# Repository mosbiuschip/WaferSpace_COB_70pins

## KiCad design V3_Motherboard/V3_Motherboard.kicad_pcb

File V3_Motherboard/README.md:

# MV3C_PCB_TEMP
Temporary View Repo for V3 Motherboard PCB (v4a_2026)

Changes from V1 Chip PCB (v3b_2025)

1. Pin bindings changed according to pin bindings .csv and WaferSpace_COB_70pins/V3_COB_Original, COB mounting footprint replaced chip socket
    a. Added Bus 1-5 pins, routed out through 2x3 header pin Breakout
    b. Removed NPAIR_4_BODY, PPAIR_4_BODY, ISINK_32 pins
    c. Changed trace width from standard .25 to .15

Further design considerations and questions

1. SOLVED: LDO - Already have voltage supply protection, is there any reason of convenience to keep LDO for 2.5V or other voltage
2. SOLVED: Power Net Switch - Is it desireable to have an aditional low drop mechanical switch for power net for chip safety
3. Feedback from V1 board - Are there any issues with original V1 design that need to be addressed

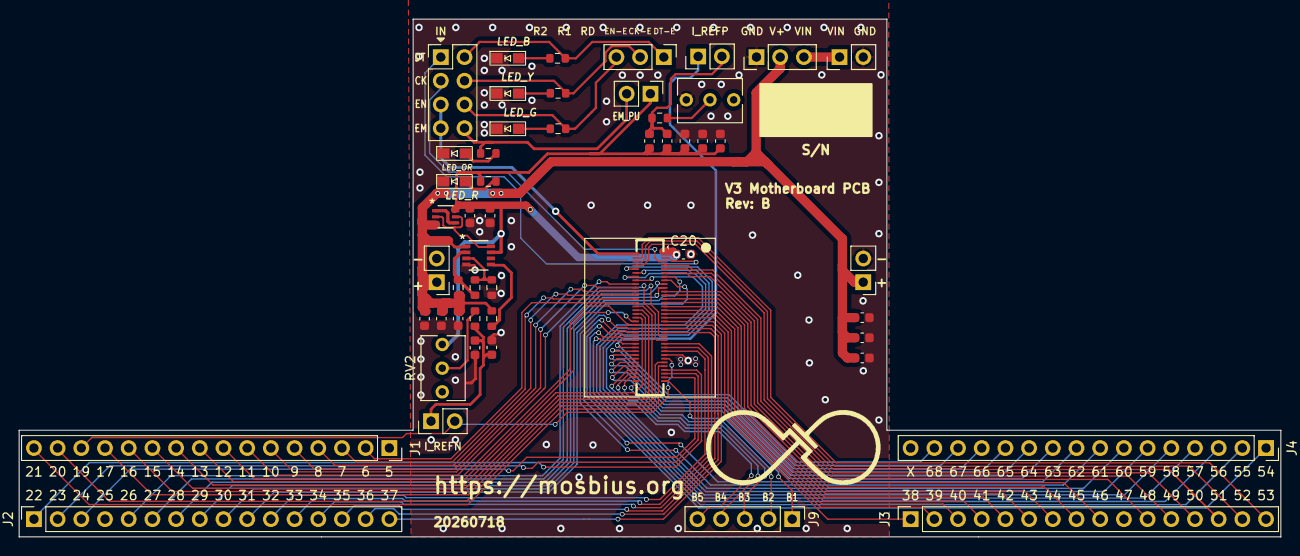
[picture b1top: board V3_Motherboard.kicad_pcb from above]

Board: 2 copper layers, 135.3 x 55.5 mm, 51 parts (0 on the bottom side), 90 nets.

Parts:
C1, C6, C8, C9, C15, C18: 1u; C_0603_1608Metric
C2, C3, C7, C10, C16, C17: 0.1u; C_0603_1608Metric
C12, C14, C19: 10u; C_0603_1608Metric
C20: 47u; C_0603_1608Metric
D1: LED_OR; SunLED_LED_XZC_0805
D2: LED_G; SunLED_LED_XZC_0805
D3: LED_Y; SunLED_LED_XZC_0805
D4: LED_B; SunLED_LED_XZC_0805
D5: LED_R; SunLED_LED_XZC_0805
J1, J2, J3, J4: Conn_01x16_Pin; PinSocket_1x16_P2.54mm_Vertical
J5, J7, J8: PINHD_1x2_Male; PinHeader_1x02_P2.54mm_Vertical
J6: Conn_01x02_Pin; PinHeader_1x02_P2.54mm_Vertical
J9: Conn_01x05_Pin; PinHeader_1x05_P2.54mm_Vertical
J10: Conn_02x04_Row_Letter_First; PinHeader_2x04_P2.54mm_Vertical
J14_GND2, J14_GND3: Conn_01x03; PinHeader_1x03_P2.54mm_Vertical
J18_VDC1: Conn_01x02; PinHeader_1x02_P2.54mm_Vertical
JP2_EN1: Jumper_2_Open; PinHeader_1x02_P2.54mm_Vertical
R7, R9, R17, R19: 330; R_0603_1608Metric
R8: 750; R_0603_1608Metric
R11, R18: 1.1k; R_0603_1608Metric
R13, R16: 0; R_0603_1608Metric
R14: 510K; R_0603_1608Metric
R15: 120K; R_0603_1608Metric
RV1, RV2: 25k_POT; Potentiometer_Bourns_3266Y_Vertical
U2: LTC4365TS8; TSOT-23_TS8_LIT
U3: UM6K34NTCN; TRANS_UM6J1_ROM
U4: P0.40_HC-PBB40C-70DS-0.4V-3.0-02_wscob

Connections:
/BUS1: J9.1, U4.35 (pad_46)
/BUS2: J9.2, U4.36 (pad_44)
/BUS3: J9.3, U4.37 (pad_43)
/BUS4: J9.4, U4.38 (pad_42)
/BUS5: J9.5, U4.39 (pad_41)
/CMFB_OTA2_INN: J4.2, U4.47 (pad_32)
/CMFB_OTA2_INP: J4.3, U4.46 (VDD_CORE)
/CMFB_OTA2_OUT: J4.1, U4.48 (pad_31)
/CM_N_IOUT_1: J1.15, U4.30 (pad_51)
/CM_N_IOUT_2: J1.16, U4.31 (pad_50)
/CM_N_IOUT_4: J2.1, U4.32 (pad_49)
/CM_N_IOUT_8: J2.2, U4.33 (pad_48)
/CM_N_IOUT_16: J2.3, U4.34 (pad_47)
/CM_N_IREF: J1.14, J7.2, U4.29 (pad_52)
/CM_N_IREF2: J2.5, U4.24 (VDD_IO)
/CM_N_IREF3: J2.6, U4.23 (pad_58)
/CM_P_IOUT_1: J4.14, U4.44 (VDD_IO)
/CM_P_IOUT_2: J4.13, U4.43 (pad_37)
/CM_P_IOUT_4: J4.12, U4.42 (pad_38)
/CM_P_IOUT_8: J4.11, U4.41 (pad_39)
/CM_P_IOUT_16: J4.10, U4.40 (pad_40)
/CM_P_IREF: J4.15, J8.1, U4.45 (GND)
/CM_P_IREF2: J4.9, U4.49 (pad_30)
/CM_P_IREF3: J4.8, U4.50 (pad_29)
/INV_TPLGY16_1INN: J3.14, U4.67 (pad_12)
/INV_TPLGY16_1INP: J3.16, U4.69 (pad_10)
/INV_TPLGY16_1OUT: J3.15, U4.68 (pad_11)
/INV_TPLGY16_2INN: J3.11, U4.6 (pad_2)
/INV_TPLGY16_2INP: J3.13, U4.4 (pad_4)
/INV_TPLGY16_2OUT: J3.12, U4.5 (pad_3)
/NMOS_4A_DRAIN: J2.8, U4.10 (GND)
/NMOS_4A_GATE: J2.7, U4.9 (VDD_IO)
/NMOS_4B_DRAIN: J2.10, U4.8 (pad_0)
/NMOS_4B_GATE: J2.9, U4.7 (pad_1)
/NPAIR_4A_DRAIN: J3.4, U4.16 (pad_65)
/NPAIR_4A_GATE: J3.5, U4.15 (pad_66)
/NPAIR_4A_SOURCE: J3.6, U4.14 (pad_67)
/NPAIR_4B_DRAIN: J3.9, U4.11 (VDD_CORE)
/NPAIR_4B_GATE: J3.8, U4.12 (pad_69)
/NPAIR_4B_SOURCE: J3.7, U4.13 (pad_68)
/NPAIR_A_DRAIN: J2.14, U4.22 (pad_59)
/NPAIR_A_GATE: J2.15, U4.21 (pad_60)
/NPAIR_A_SOURCE: J2.16, U4.20 (pad_61)
/NPAIR_B_DRAIN: J3.3, U4.17 (pad_64)
/NPAIR_B_GATE: J3.2, U4.18 (GND)
/NPAIR_B_SOURCE: J3.1, U4.19 (PWR_AUX)
/OTA_N_INN: J2.12, U4.26 (pad_55)
/OTA_N_INP: J2.11, U4.27 (pad_54)
/OTA_N_OUT: J2.13, U4.25 (GND)
/PMOS_4A_DRAIN: J4.4, U4.63 (pad_16)
/PMOS_4A_GATE: J4.5, U4.64 (pad_15)
/PMOS_4B_DRAIN: J4.6, U4.65 (pad_14)
/PMOS_4B_GATE: J4.7, U4.66 (pad_13)
/PPAIR_4A_DRAIN: J1.2, U4.57 (pad_22)
/PPAIR_4A_GATE: J1.3, U4.58 (pad_21)
/PPAIR_4A_SOURCE: J1.4, U4.59 (pad_20)
/PPAIR_4B_DRAIN: J1.7, U4.62 (VDD_IO)
/PPAIR_4B_GATE: J1.6, U4.61 (GND)
/PPAIR_4B_SOURCE: J1.5, U4.60 (pad_19)
/PPAIR_A_DRAIN: J1.8, U4.51 (pad_28)
/PPAIR_A_GATE: J1.9, U4.52 (pad_27)
/PPAIR_A_SOURCE: J1.10, U4.53 (GND)
/PPAIR_B_DRAIN: J1.13, U4.56 (pad_23)
/PPAIR_B_GATE: J1.12, U4.55 (pad_24)
/PPAIR_B_SOURCE: J1.11, U4.54 (PWR_AUX)
CLK: J10.3, U4.3 (pad_5)
CLK_CVRT_3.3V: J10.4, J14_GND2.2, R8.1
DATA: J10.1, U4.2 (pad_6)
DATA_CVRT_3.3V: J10.2, J14_GND2.1, R9.1
ENABLE: J10.5, J10.7, U4.70 (pad_9)
EN_CVRT_3.3V: J10.6, J14_GND2.3, R7.1
EN_MAN_3.3V: J10.8, JP2_EN1.2 (B), R19.1
GND: C1.2, C2.2, C6.2, C7.2, C9.2, C10.2, C12.2, C14.2, C15.2, C16.2, C17.2, C18.2, C19.2, C20.2, D1.1 (K), D2.1 (K), D3.1 (K), D4.1 (K), D5.1 (K), J5.2, J6.2, J14_GND3.1, J18_VDC1.2, R15.2, RV1.3, U2.4 (GND), U4.28 (pad_53)
unnamed: C1.1, C2.1, J7.1, R18.2
unnamed: C3.2, C8.2, J8.2, R11.2
unnamed: D1.2 (A), R19.2
unnamed: D2.2 (A), R7.2
unnamed: D3.2 (A), R8.2
unnamed: D4.2 (A), R9.2
unnamed: D5.2 (A), R17.2
unnamed: R11.1, RV1.2
unnamed: R18.1, RV2.2
unnamed: U2.8 (GATE), U3.2, U3.5
unnamed: R14.2, R15.1, U2.3 (OV)
unnamed: R13.2, R14.1, U2.2 (UV)
unnamed: R16.2, U2.5 (~SHDN)
unnamed: U3.1, U3.4
VD: C9.1, C10.1, C12.1, C14.1, C15.1, C16.1, J5.1, J6.1, J14_GND3.2, R13.1, R16.1, U2.1 (Vin), U3.3
VDD: C3.1, C6.1, C7.1, C8.1, C17.1, C18.1, C19.1, C20.1, JP2_EN1.1 (A), R17.1, RV2.1, U2.7 (Vout), U3.6, U4.1 (pad_7)
VIN: J14_GND3.3, J18_VDC1.1

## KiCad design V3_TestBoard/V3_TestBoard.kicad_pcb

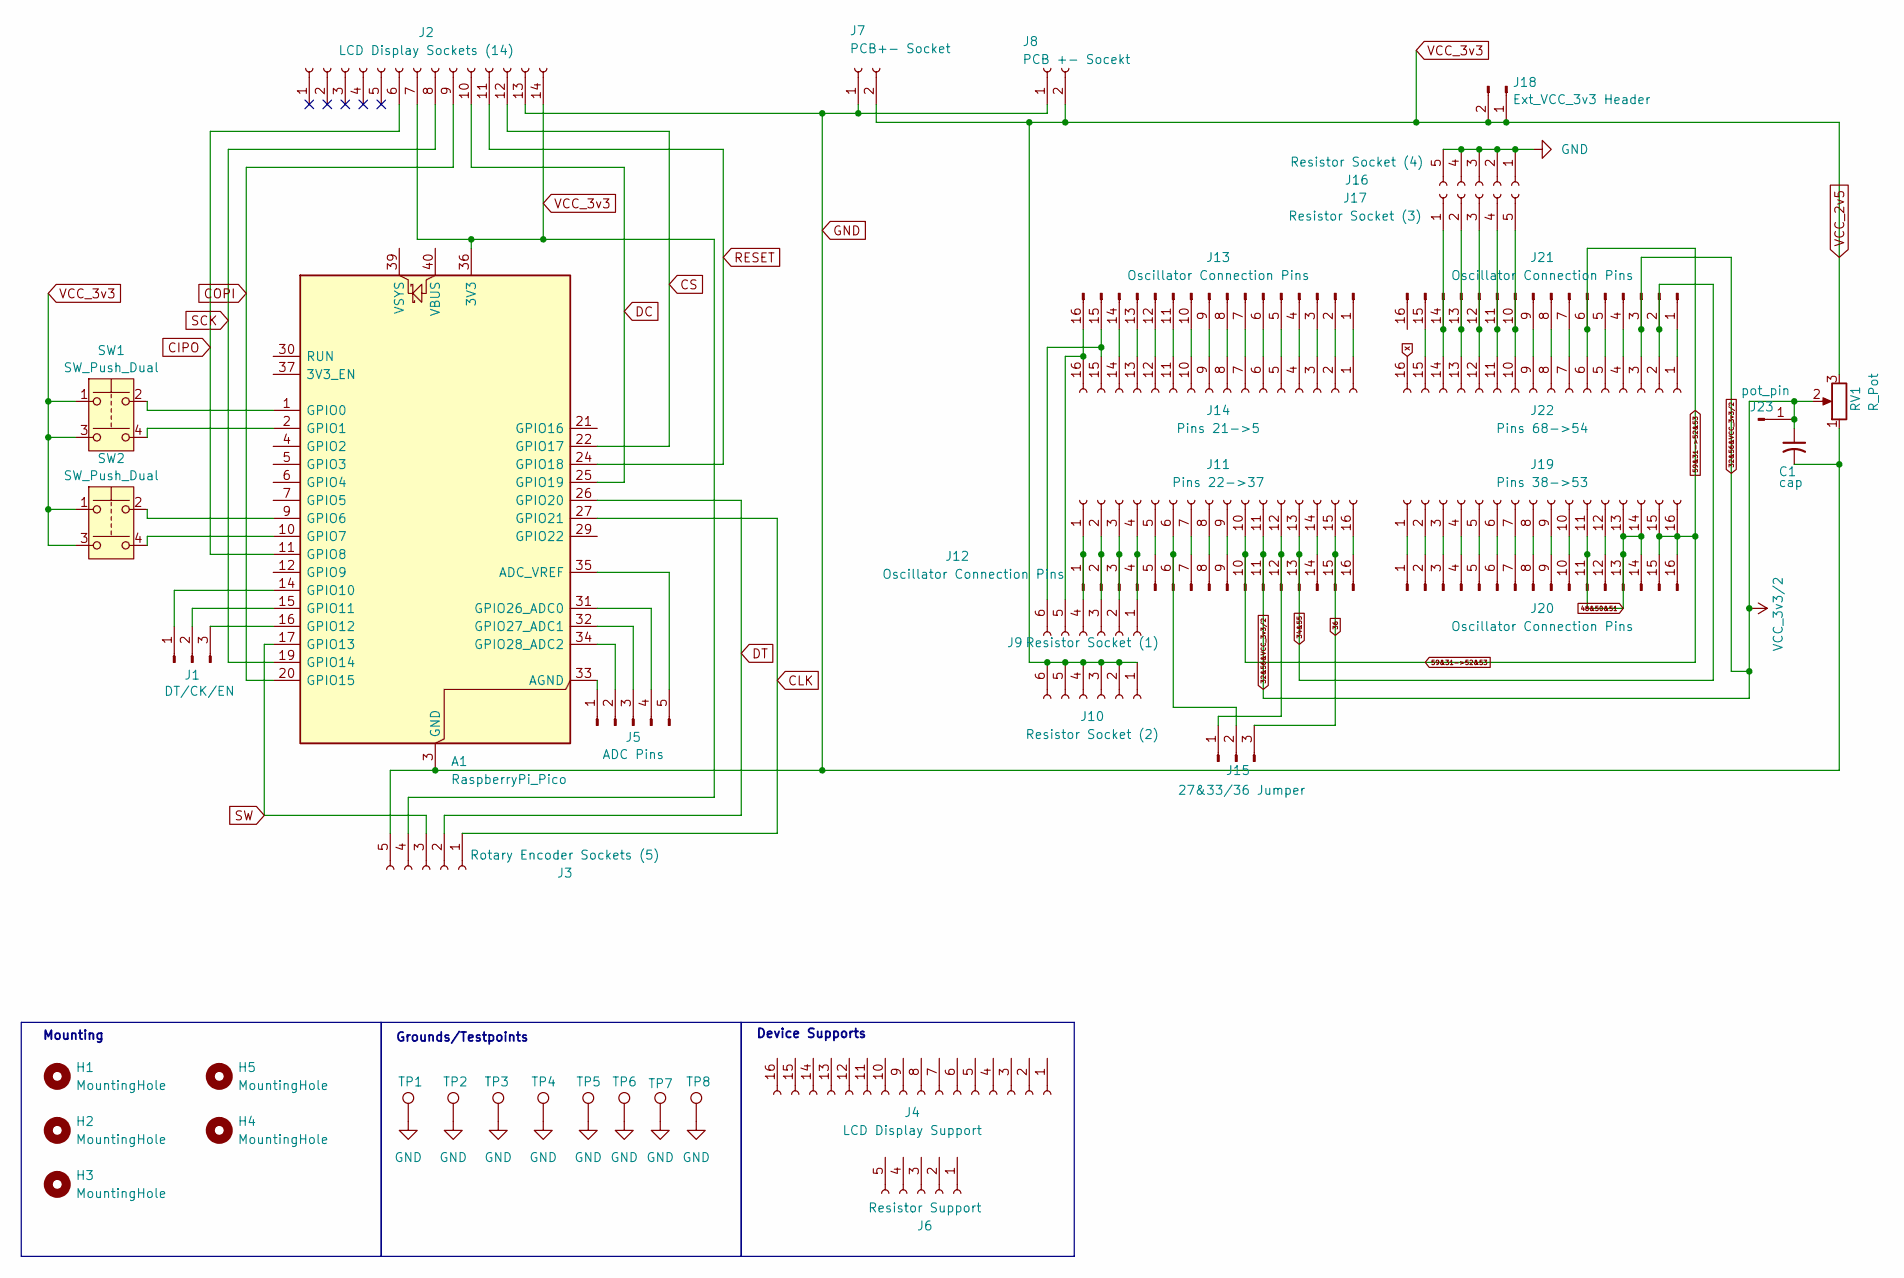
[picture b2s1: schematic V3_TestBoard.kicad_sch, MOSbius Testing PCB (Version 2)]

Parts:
A1: RaspberryPi_Pico; RaspberryPi_Pico_Common_THT
C1: cap; C_Axial_L3.8mm_D2.6mm_P7.50mm_Horizontal
H1, H2, H3, H4, H5: MountingHole; MountingHole_3.2mm_M3_DIN965
J1: DT/CK/EN; PinHeader_1x03_P2.54mm_Vertical
J2: LCD Display Sockets (14); PinSocket_1x14_P2.54mm_Vertical
J3: Rotary Encoder Sockets (5); PinSocket_1x05_P2.54mm_Vertical
J4: LCD Display Support; PinSocket_1x16_P2.54mm_Vertical
J5: ADC Pins; PinSocket_1x05_P2.54mm_Vertical
J6: Resistor Support; PinSocket_1x05_P2.54mm_Vertical
J7: PCB+- Socket; PinSocket_1x02_P2.54mm_Vertical
J8: PCB +- Socekt; PinSocket_1x02_P2.54mm_Vertical
J9: Resistor Socket (1); PinSocket_1x06_P2.54mm_Vertical
J10: Resistor Socket (2); PinSocket_1x06_P2.54mm_Vertical
J11: Pins 22->37; PinSocket_1x16_P2.54mm_Vertical
J12, J13, J20, J21: Oscillator Connection Pins; PinHeader_1x16_P2.54mm_Vertical
J14: Pins 21->5; PinSocket_1x16_P2.54mm_Vertical
J15: 27&33/36 Jumper; PinHeader_1x03_P2.54mm_Vertical
J16: Resistor Socket (4); PinSocket_1x05_P2.54mm_Vertical
J17: Resistor Socket (3); PinSocket_1x05_P2.54mm_Vertical
J18: Ext_VCC_3v3 Header; PinHeader_1x02_P2.54mm_Vertical
J19: Pins 38->53; PinSocket_1x16_P2.54mm_Vertical
J22: Pins 68->54; PinSocket_1x16_P2.54mm_Vertical
J23: pot_pin; PinHeader_1x01_P2.54mm_Vertical
RV1: R_Pot; Potentiometer_ACP_CA6-H2,5_Horizontal
SW1, SW2: SW_Push_Dual; SW_Push_2P1T_Toggle_CK_PVA1xxH4xxxxxxV2
TP1, TP2, TP3, TP4, TP5, TP6, TP7, TP8: TestPoint_Bridge_Pitch2.54mm_Drill1.3mm

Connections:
32&56&VCC_3v3/2: C1.1, J11.11, J12.11, J21.3, J22.3, J23.1, RV1.2
34&55: J11.13, J12.13, J21.2, J22.2
36: J11.15, J12.15, J15.3
48&50&51: J19.11, J19.13, J19.14, J20.11, J20.13, J20.14
59&31->52&53: J11.10, J12.10, J19.15, J19.16, J20.15, J20.16, J21.6, J22.6
CIPO: A1.11 (GPIO8), J2.6
CLK: A1.27 (GPIO21), J3.1
COPI: A1.20 (GPIO15), J2.9
CS: A1.22 (GPIO17), J2.12
DC: A1.25 (GPIO19), J2.10
DT: A1.26 (GPIO20), J3.2
GND: A1.3 (GND), A1.8 (GND), A1.13 (GND), A1.18 (GND), A1.23 (GND), A1.28 (GND), A1.38 (GND), C1.2, J2.13, J3.5, J7.1, J8.1, J16.1, J16.2, J16.3, J16.4, J16.5, RV1.1, TP1.1, TP2.1, TP3.1, TP4.1, TP5.1, TP6.1, TP7.1, TP8.1
unnamed: A1.35 (ADC_VREF), J5.5
unnamed: A1.33 (AGND), J5.1
unnamed: A1.1 (GPIO0), SW1.2
unnamed: A1.2 (GPIO1), SW1.4
unnamed: A1.9 (GPIO6), SW2.2
unnamed: A1.10 (GPIO7), SW2.4
unnamed: A1.14 (GPIO10), J1.1
unnamed: A1.15 (GPIO11), J1.2
unnamed: A1.16 (GPIO12), J1.3
unnamed: A1.31 (GPIO26_ADC0), J5.4
unnamed: A1.32 (GPIO27_ADC1), J5.3
unnamed: A1.34 (GPIO28_ADC2), J5.2
unnamed: J9.4, J11.1, J12.1
unnamed: J9.3, J11.2, J12.2
unnamed: J9.2, J11.3, J12.3
unnamed: J9.1, J11.4, J12.4
unnamed: J11.5, J12.5
unnamed: J11.6, J12.6, J15.2
unnamed: J11.7, J12.7
unnamed: J11.8, J12.8
unnamed: J11.9, J12.9
unnamed: J11.12, J12.12, J15.1
unnamed: J11.14, J12.14
unnamed: J11.16, J12.16
unnamed: J13.1, J14.1
unnamed: J13.2, J14.2
unnamed: J13.3, J14.3
unnamed: J13.4, J14.4
unnamed: J13.5, J14.5
unnamed: J13.6, J14.6
unnamed: J13.7, J14.7
unnamed: J13.8, J14.8
unnamed: J13.9, J14.9
unnamed: J13.10, J14.10
unnamed: J13.11, J14.11
unnamed: J13.12, J14.12
unnamed: J13.13, J14.13
unnamed: J13.14, J14.14
unnamed: J9.6, J13.15, J14.15
unnamed: J9.5, J13.16, J14.16
unnamed: J17.1, J21.14, J22.14
unnamed: J17.2, J21.13, J22.13
unnamed: J17.3, J21.12, J22.12
unnamed: J17.4, J21.11, J22.11
unnamed: J17.5, J21.10, J22.10
unnamed: J19.1, J20.1
unnamed: J19.2, J20.2
unnamed: J19.3, J20.3
unnamed: J19.4, J20.4
unnamed: J19.5, J20.5
unnamed: J19.6, J20.6
unnamed: J19.7, J20.7
unnamed: J19.8, J20.8
unnamed: J19.9, J20.9
unnamed: J19.10, J20.10
unnamed: J19.12, J20.12
unnamed: J21.1, J22.1
unnamed: J21.4, J22.4
unnamed: J21.5, J22.5
unnamed: J21.7, J22.7
unnamed: J21.8, J22.8
unnamed: J21.9, J22.9
unnamed: J21.15, J22.15
RESET: A1.24 (GPIO18), J2.11
SCK: A1.19 (GPIO14), J2.8
SW: A1.17 (GPIO13), J3.3
VCC_2v5: A1.36 (3V3), J2.7, J2.14, J3.4, J7.2, J8.2, J10.1, J10.2, J10.3, J10.4, J10.5, J10.6, J18.1, J18.2, RV1.3, SW1.1, SW1.3, SW2.1, SW2.3
X: J22.16

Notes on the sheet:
Device Supports
Grounds/Testpoints
Mounting

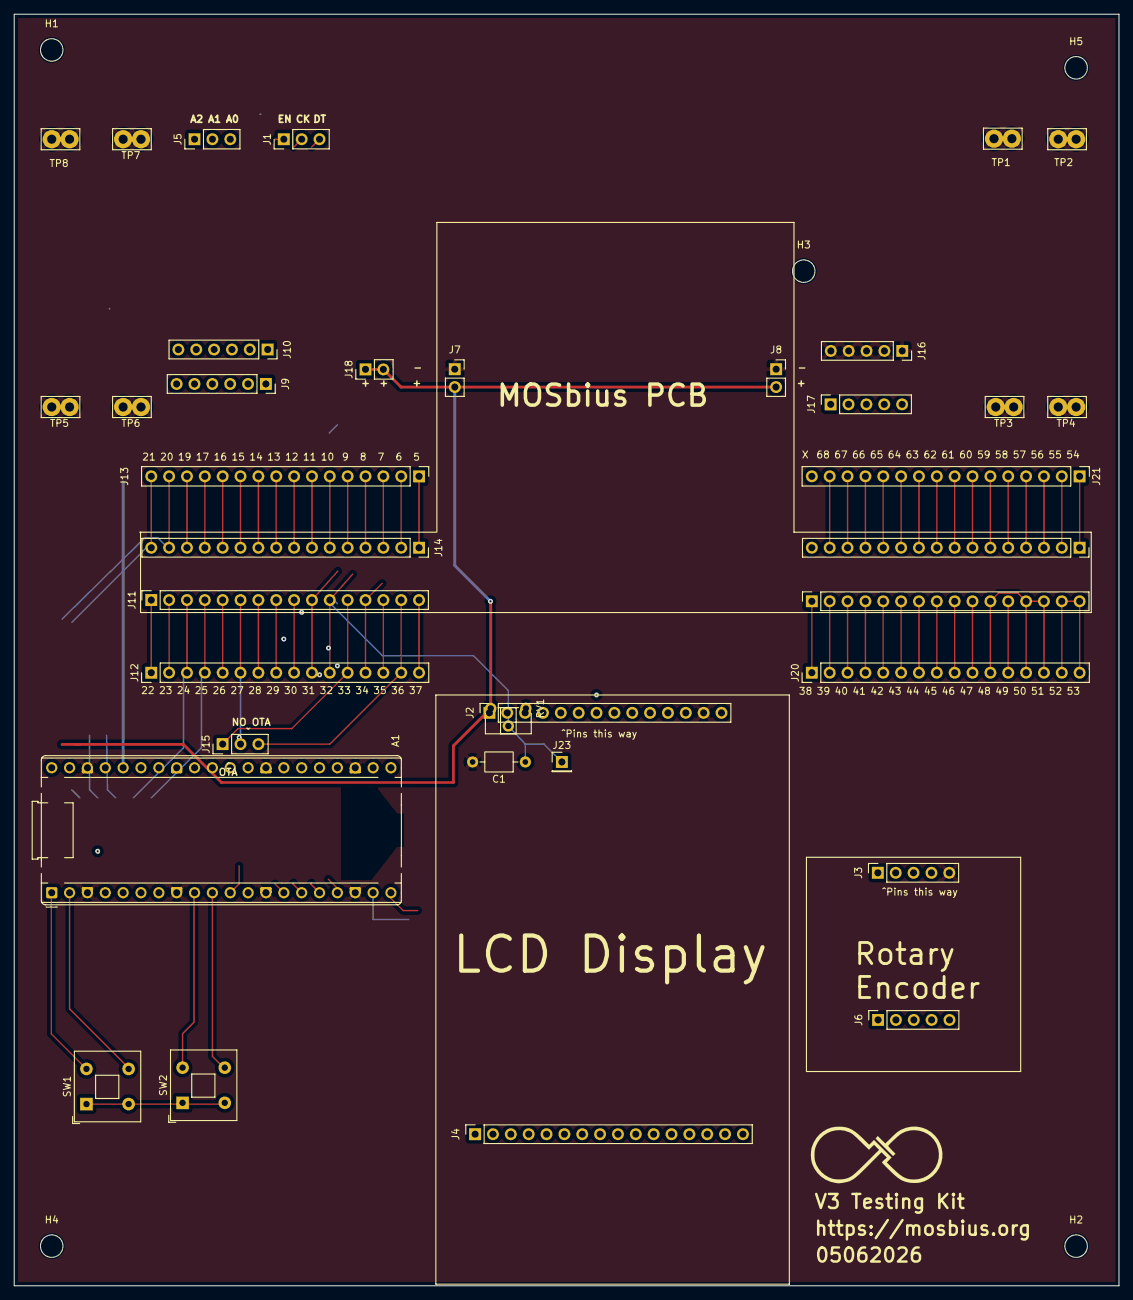
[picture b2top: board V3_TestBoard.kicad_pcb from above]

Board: 2 copper layers, 157.2 x 180.9 mm, 41 parts (0 on the bottom side), 77 nets.

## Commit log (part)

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2025-10-19 1019 XP uploaded mezzanine PCB design
    there are 2 VDD Pins on Chip (PIN29 and PIN30), 4 VSS Pins on Chip (PIN1, PIN20, PIN38 and PIN57), and 68 Signal Pins.
2025-10-26 1026 round COB bondpad
2025-11-08 updates for round_PAD structure design includes PCB design (1108)
2025-11-08 updates for round-PAD 1108
2025-11-19 update of mezzanine round bond PCB 1118
2025-11-29 update for round board 1129
2026-03-05 XP updates 4th May 2026
2026-03-05 XP updates the name of the design
    rename to 'V3_COB'
2026-03-05 XP update in V3_COB (clean up works)
2026-03-06 XP 5th March update
2026-03-13 XP uploaded Gerber & Drill files of V3_COB
2026-03-13 XP update in layout for V3_COB
2026-03-18 XP added new COB design based on original case (square shape)
2026-03-18 V3_COB clean up
2026-03-18 V3_COB_Original Gerber & Drill files
2026-03-27 xp re-route the wire for original design to make chip in correct direction
2026-03-27 clean old gerber & drill files
2026-03-28 XP update org design gerber & drill files
2026-03-30 updates on 3/30
2026-03-30 update gerber files
2026-03-30 update in gerber files 2
2026-03-30 clean up in gerber files 1
2026-03-30 clean up gerber files 2
2026-04-02 mosbius logo update
2026-04-02 update mosbius logo and gerber files
2026-04-18 create panel
2026-04-19 uncheck auto-fill on export
2026-04-20 extend v-cut lines for jlc
2026-04-20 Updated Bus Pin Placement for Bottom Mounting
2026-04-23 Added simplified V3 Motherboard PCB
2026-05-06 Added copy of V2 test board repo, began modifications for V3
2026-05-13 Updated V3_Motherboard to fab revision
